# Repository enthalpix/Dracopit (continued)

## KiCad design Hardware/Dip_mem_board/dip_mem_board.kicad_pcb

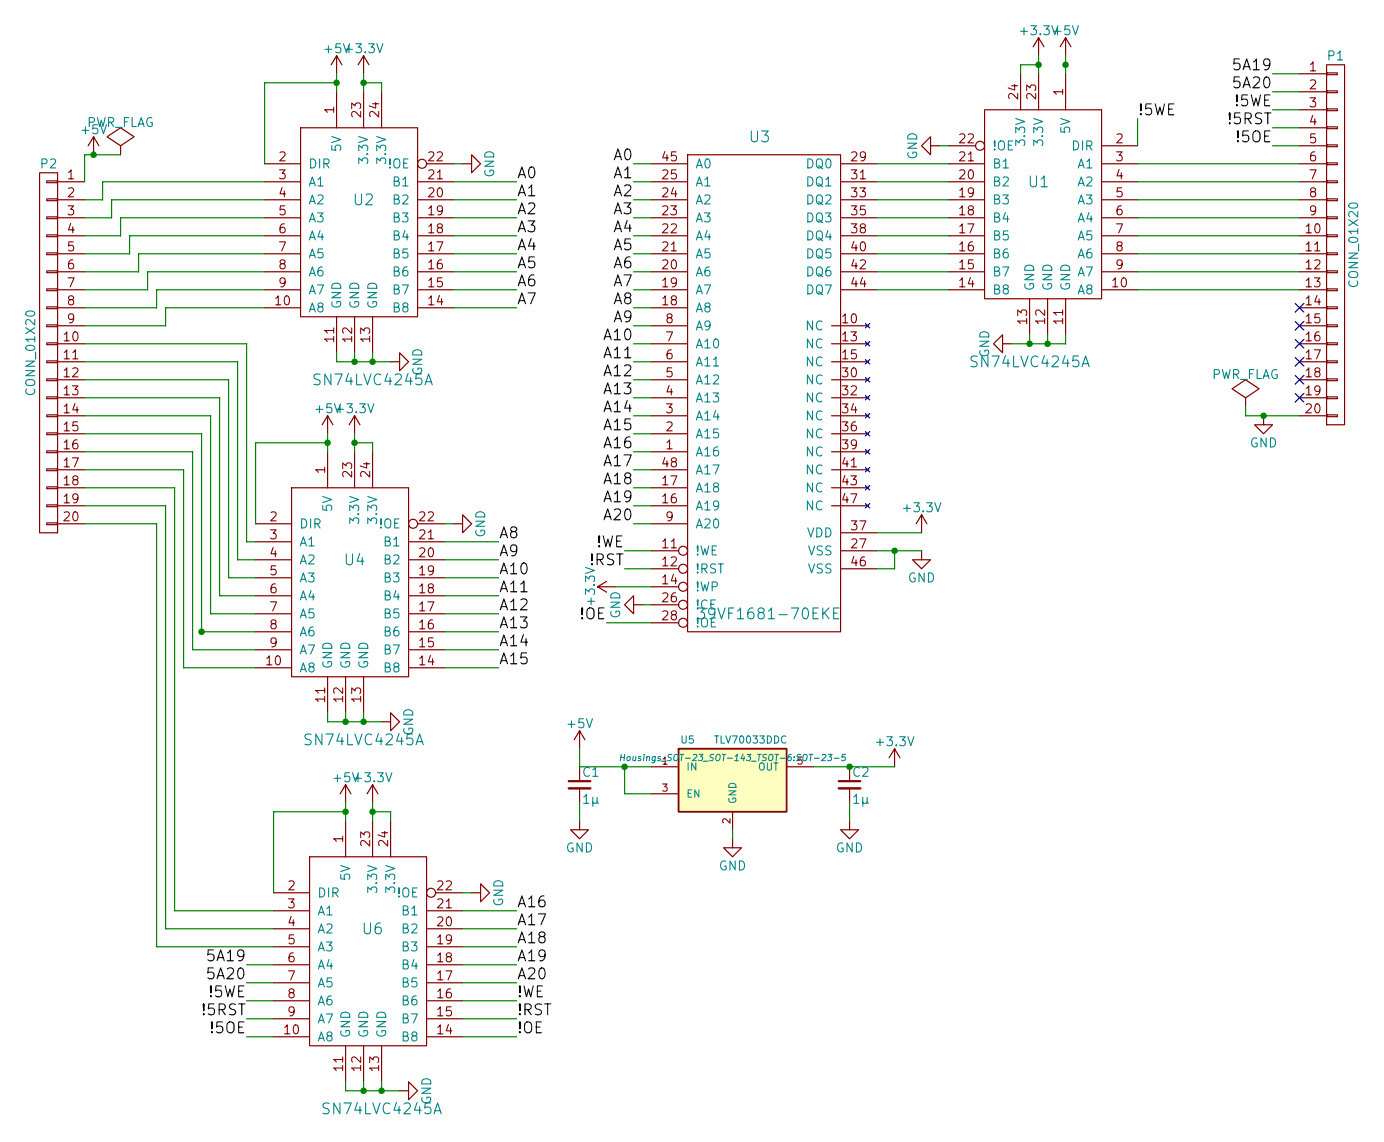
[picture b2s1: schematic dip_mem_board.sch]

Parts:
C1, C2: 1µ; C_0805_HandSoldering
P1, P2: CONN_01X20; Pin_Header_Straight_1x20
U1, U2, U4, U6: SN74LVC4245A; SSOP-24_3.9x8.7mm_Pitch0.635mm
U3: 39VF1681-70EKE; TSOP-48
U5: TLV70033DDC; SOT-23-5

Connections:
+3V3: C2.1, U1.23 (3.3V), U1.24 (3.3V), U2.23 (3.3V), U2.24 (3.3V), U3.14 (!WP), U3.37 (VDD), U4.23 (3.3V), U4.24 (3.3V), U5.5 (OUT), U6.23 (3.3V), U6.24 (3.3V)
+5V: C1.1, P2.1, U1.1 (5V), U2.1 (5V), U2.2 (DIR), U4.1 (5V), U4.2 (DIR), U5.1 (IN), U5.3 (EN), U6.1 (5V), U6.2 (DIR)
/5A19: P1.1, U6.6 (A4)
/5A20: P1.2, U6.7 (A5)
/!5OE: P1.5, U6.10 (A8)
/!5RST: P1.4, U6.9 (A7)
/!5WE: P1.3, U1.2 (DIR), U6.8 (A6)
/!OE: U3.28 (!OE), U6.14 (B8)
/!RST: U3.12 (!RST), U6.15 (B7)
/!WE: U3.11 (!WE), U6.16 (B6)
/A0: U2.21 (B1), U3.45 (A0)
/A1: U2.20 (B2), U3.25 (A1)
/A2: U2.19 (B3), U3.24 (A2)
/A3: U2.18 (B4), U3.23 (A3)
/A4: U2.17 (B5), U3.22 (A4)
/A5: U2.16 (B6), U3.21 (A5)
/A6: U2.15 (B7), U3.20 (A6)
/A7: U2.14 (B8), U3.19 (A7)
/A8: U3.18 (A8), U4.21 (B1)
/A9: U3.8 (A9), U4.20 (B2)
/A10: U3.7 (A10), U4.19 (B3)
/A11: U3.6 (A11), U4.18 (B4)
/A12: U3.5 (A12), U4.17 (B5)
/A13: U3.4 (A13), U4.16 (B6)
/A14: U3.3 (A14), U4.15 (B7)
/A15: U3.2 (A15), U4.14 (B8)
/A16: U3.1 (A16), U6.21 (B1)
/A17: U3.48 (A17), U6.20 (B2)
/A18: U3.17 (A18), U6.19 (B3)
/A19: U3.16 (A19), U6.18 (B4)
/A20: U3.9 (A20), U6.17 (B5)
GND: C1.2, C2.2, P1.20, U1.11 (GND), U1.12 (GND), U1.13 (GND), U1.22 (!OE), U2.11 (GND), U2.12 (GND), U2.13 (GND), U2.22 (!OE), U3.26 (!CE), U3.27 (VSS), U3.46 (VSS), U4.11 (GND), U4.12 (GND), U4.13 (GND), U4.22 (!OE), U5.2 (GND), U6.11 (GND), U6.12 (GND), U6.13 (GND), U6.22 (!OE)
unnamed: P1.6, U1.3 (A1)
unnamed: P1.7, U1.4 (A2)
unnamed: P1.8, U1.5 (A3)
unnamed: P1.9, U1.6 (A4)
unnamed: P1.10, U1.7 (A5)
unnamed: P1.11, U1.8 (A6)
unnamed: P1.12, U1.9 (A7)
unnamed: P1.13, U1.10 (A8)
unnamed: P2.2, U2.3 (A1)
unnamed: P2.3, U2.4 (A2)
unnamed: P2.4, U2.5 (A3)
unnamed: P2.5, U2.6 (A4)
unnamed: P2.6, U2.7 (A5)
unnamed: P2.7, U2.8 (A6)
unnamed: P2.8, U2.9 (A7)
unnamed: P2.9, U2.10 (A8)
unnamed: P2.10, U4.3 (A1)
unnamed: P2.11, U4.4 (A2)
unnamed: P2.12, U4.5 (A3)
unnamed: P2.13, U4.6 (A4)
unnamed: P2.14, U4.7 (A5)
unnamed: P2.15, U4.8 (A6)
unnamed: P2.16, U4.9 (A7)
unnamed: P2.17, U4.10 (A8)
unnamed: P2.18, U6.3 (A1)
unnamed: P2.19, U6.4 (A2)
unnamed: P2.20, U6.5 (A3)
unnamed: U1.14 (B8), U3.44 (DQ7)
unnamed: U1.15 (B7), U3.42 (DQ6)
unnamed: U1.16 (B6), U3.40 (DQ5)
unnamed: U1.17 (B5), U3.38 (DQ4)
unnamed: U1.18 (B4), U3.35 (DQ3)
unnamed: U1.19 (B3), U3.33 (DQ2)
unnamed: U1.20 (B2), U3.31 (DQ1)
unnamed: U1.21 (B1), U3.29 (DQ0)

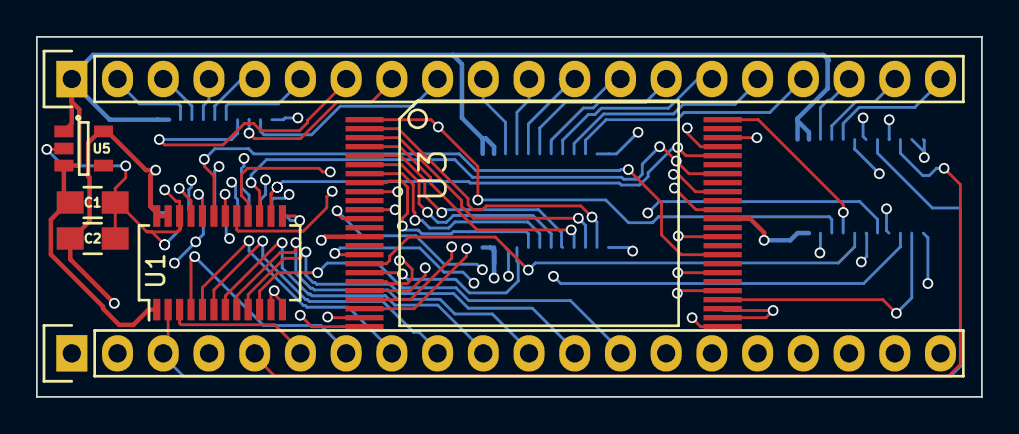
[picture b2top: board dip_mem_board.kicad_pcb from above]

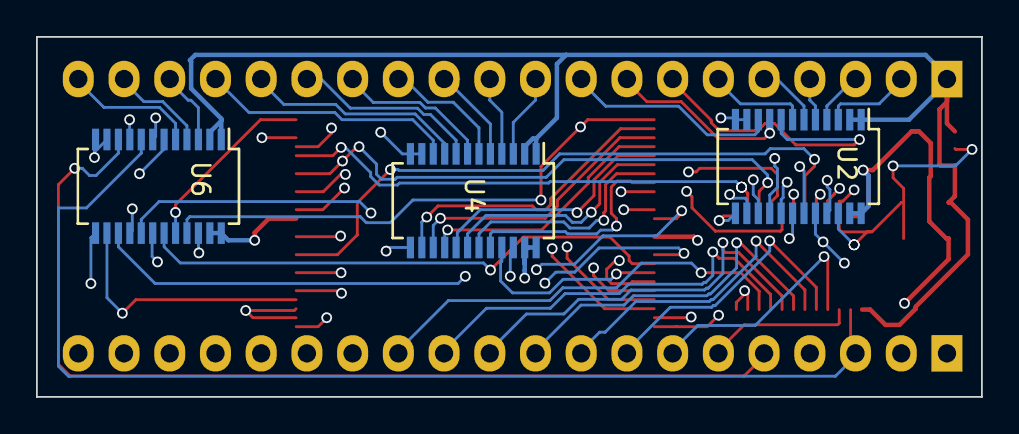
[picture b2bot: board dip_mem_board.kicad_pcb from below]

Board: 4 copper layers, 52.5 x 20.0 mm, 10 parts (3 on the bottom side), 67 nets.

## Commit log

2015-09-03 Initial file upload
    Schematics upload
2015-09-03 Added voice section dividers
    Added voice section frequency dividers
2015-09-03 Connectors
    Connectors for transfering signal to the analog board
2015-09-03 ERC
    Corrections after ERC pass
2015-09-04 Components association
2015-09-04 Decoupling cap
2015-09-15 Removed the fm synthesis
    Removed the fm synthesis to keep project manageable on the remaining
    time (<2month)
2015-09-16 Schematic ERC corrections
2015-09-17 Pcb design
2015-09-17 Main pcb done
2015-09-18 First activity board
2015-09-18 Connector correction
